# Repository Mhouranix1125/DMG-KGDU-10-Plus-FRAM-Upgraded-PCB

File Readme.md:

### Welcome! PLEASE READ EVERYTHING!

First: Shoutout to HDR. His work was extremely vital in completing this project. Take a look at his github and check out some of the cool projects he has worked on!

[HDR's Github](https://github.com/HDR)

Second: You do this entire transfer at your own risk. I am not responsible for anything that happens to your game as a result of taking on this project. This is not a beginner task, and should definitely not be taken on as a first-time solder project.  I am not affiliated with any of the companies mentioned here. I do not do this for profit. This is just a neat little thing I decided to work on. 

This project is open source. Users may use this work to iterate, or improve upon it. In doing so, please make sure you follow the Creative Common License linked below. Out of respect for HDR. Do not be a bad actor. your compliance is expected, and appreciated. DMG-KGDU-10 is an original Nintendo PCB design. I take no credit for that. 

[Creative Commons License](https://creativecommons.org/licenses/by-nc-sa/4.0/)

### What is this project about?

In simple terms - This project is an upgraded replacement circuit board for games like Pokémon Gold, Silver, and Crystal. This board utilizes FRAM instead of SRAM so you can save your games without the need for a battery. The battery is still required for the real time clock (RTC) to function. But the good news is you will not lose any save data when the battery does die. This also features a battery retainer, so you can place a CR2025 into the slot without the need for solder tabs. This also enables you to use BRAND NAME batteries. The batteries most users buy for their games have those yellow rings around them and are absolutely terrible and volatile. Brand Name batteries are a more reliable choice and will last MUCH longer. This board was designed with the United States version of the games in mind. I created this board for a few reasons. 

1. SRAM is annoying and I hate that my save data was at the mercy of a simple coin cell battery. This fixes that and allows for a very clean and professional looking mod without wires running all over the place.

2. I see tons of reddit posts of people posting their Pokemon Gold, Silver, or Crystal games in less than stellar condition. Sure, you can use jumper wires, and if you like that, it's all you. Some are beyond repair due to corrosion, broken traces, or just problems that aren't solvable. If the ROM IC, and MBC3 mapper are in good shape. This board will definitely save your game. Your games are not broken if your circuit board is in bad shape!

3. To learn.

### How can I get my hands on these boards?

In order to get your hands on these boards, you will need to download this project zip, or clone it using GIT. One of the files labeled DMG-KGDU-10+_Gerber.zip Is the completed output of the circuit board. There are a few websites you can upload this to in order to get these boards made. they are not that expensive. These are the ones I use often. But feel free to use another if you’re comfortable with them. 

Note: PLEASE ORDER THESE BOARDS WITH THE FOLLOWING SPECIFICATIONS. IF YOU DO NOT ORDER THEM CORRECTLY, THEY WILL NOT WORK, OR WILL NOT FIT!

* Thickness: 0.8mm
* Color: Your choice! Have fun!
* Surface Finish: (ENIG or Immersion Gold. They’re the same thing) , or Hard Gold (expensive). DO NOT USE ANY OTHER OPTION. 
* Castellated Holes: No
* Copper Weight: 1oz is fine. 2oz is nice but not needed.
* Golden Fingers: Yes 
* 45° finger chamfered

1. [JLCPCB:](https://jlcpcb.com/)

o This company is based in China, and has very good pricing on boards so long as you choose either green or purple. I find the best bang for your buck to be 10 boards as it's not that much more expensive than 5.

2. [Elecrow:](https://www.elecrow.com/)

o This company is based in China, the pricing is great, and pricing is similar to JLCPCB and seems consistent across all colors. So I love these guys quite a bit. 

o Note: If using Elecrow, you will need to send them an email to specify that you want Golden Fingers, and beveled 45° finger chamfered. Just give them your order number after you place it. 

3. [Osh Park:](https://oshpark.com/shared_projects/EM2j1Td4)

o Osh Park is a USA based company. Their online gerber viewer and order process is very easy. But your options are very limited. You can only get your boards in their signature deep purple color, which are quite nice. They’re also the most expensive. Their quality is good. You get less PCB’s for your money, and I noticed that it could still take a while for them to come in.

o When you order, choose the option that says: 2 oz copper, 0.8mm thickness and you should be all set. Their ordering process is more streamlined. 

### Materials

You will need the following materials to complete this build. Feel free to source these from wherever you’d like. I recommend [Digikey](https://digikey.com), or [Mouser](https://mouser.com) for most parts. just make sure the sizes for the capacitors and resistors are correct. Double check everything. 

**Bill Of Materials:**

| Reference | Part | Description | Type |
|-|-|-|-|
| U1 | Original ROM | The lower Right chip. This is the chip that holds your game and is needed from the original board. | 44 Pins |
| U2 | MBC3 | Memory Bank Controller. You can only get this from an original Cartridge | LQFP-32 |
| U3 | FM18W08 | 256kbit FRAM | SOIC-28 |
| U4 | BA6129AF | Battery Reset IC. | Get From Original Cartridge or AliExpress | SOIC-8 |
| U5 | 74LVC1G32GV,125 | 2-input OR Gate | TSOP-5 |
| C1, C2, C3, C6, C7 | CL10B104KO8NNNC | 0.1uF Capacitor | 0603 |
| C4, C5 | CL10C150JB8NNNC | 15pF Capacitor | 0603 |
| R1 | RC0603FR-07330KL | 330K Ω Resistor | 0603 |
| R2 | RC0603FR-0710KL | 10K Ω Resistor | 0603 |
| R3 | RC0603FR-071KL | 1K Ω Resistor | 0603 |
| X1 | R26-32.768-12.5-10PPM 20PPM seems to work fine as well. | 32.768 kHz Crystal. | Buy or get from original Cartridge |
| RTC Crystal | Batt 2025 | BK-6219-TR | CR2025 Battery Retainer | Battery Retainer |

Some Tips

1). This should not be your first major solder project. Do not attempt to do this without any practice, or you risk ruining your game. 

2). Everything is pretty straight forward. Make sure you’re good with working on small components. Capacitors and resistors are not easy to solder if you’re new to this. Solder paste and hot air can help you out a lot with that process. 

3). The CR2025 battery may sometimes may not make amazing contact with the large circle pad. This is because it is ever so slightly recessed into the board. This can be fixed in a variety of ways. Super easy, and is pretty much a non issue if you just follow one of the following two ways.

My way of solving this issue is cutting out a thin piece of nickel strip (I try to make it circular in shape, and a bit smaller than the edges of the circle pad. And I lay it down flat and solder it in place before installing the BK-6219-TR retainer. Make sure you solder in the retainer so you can place the battery in from the top side of the board. If you do it upside down, getting the battery in will be annoying because the ROM IC gets in the way. 

Another way, if you don’t want to cover the pad with solder is Makhos way. Makho uses a piece of copper tape on the circle pad, rather than soldering in the nickel strip that I use. It’s nice if you don’t want to get solder on the circle pad. I personally don’t mind but the choice is yours. 

Good luck! Be sure to post your successes, and feel free to ask me any questions!

### Images

# Front

# Back

### Changes

Rev 1.1 
- Removed R1 Jumper Resistor. It was not needed.
- Added Text for some parts to help with clarity. The BOM should still be the ultimate source for info. 
- Moved a few capacitors around so they're easier to manage.
- Moved R3 so it would be easier to manage once the battery retainer is soldered in if need be.
- General cleanup.

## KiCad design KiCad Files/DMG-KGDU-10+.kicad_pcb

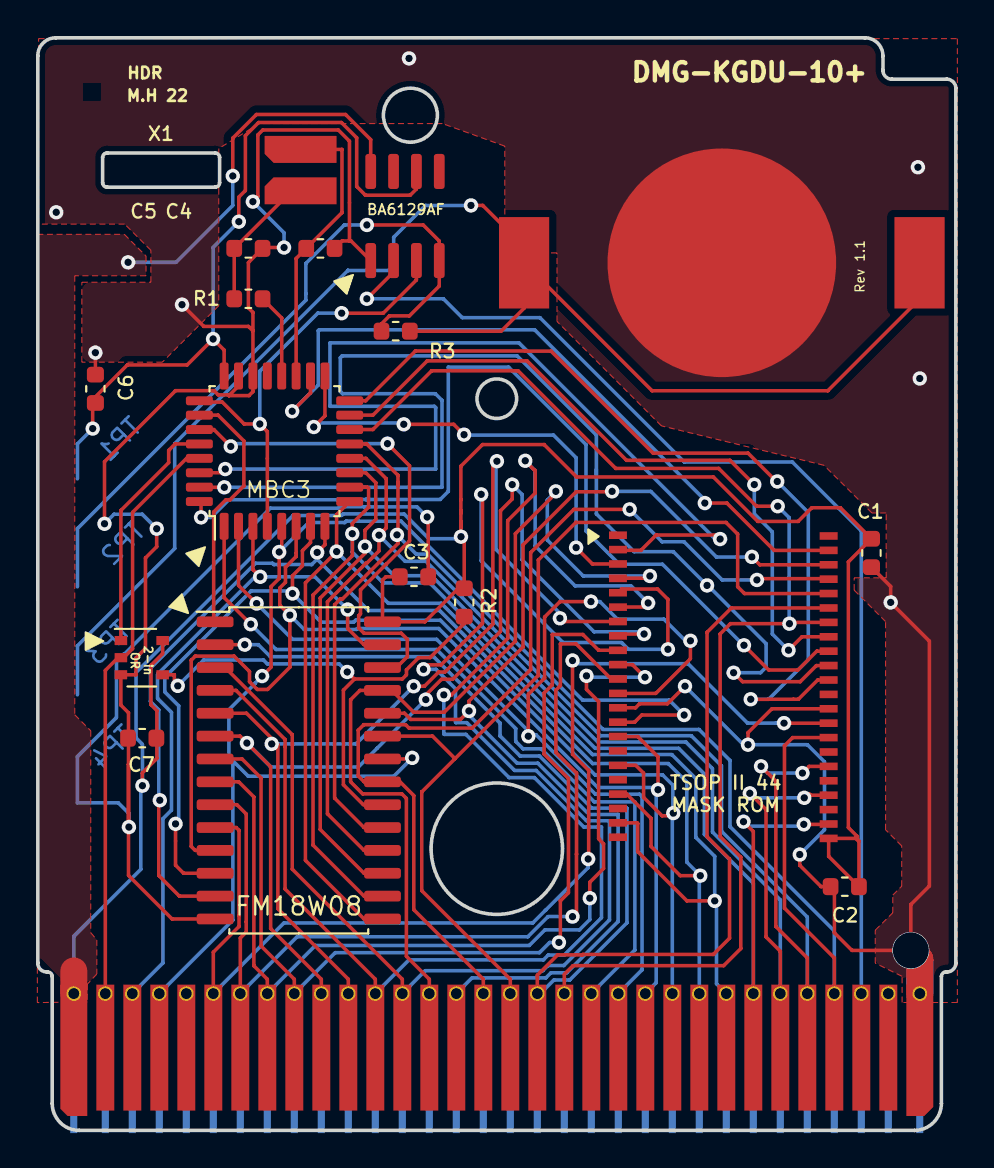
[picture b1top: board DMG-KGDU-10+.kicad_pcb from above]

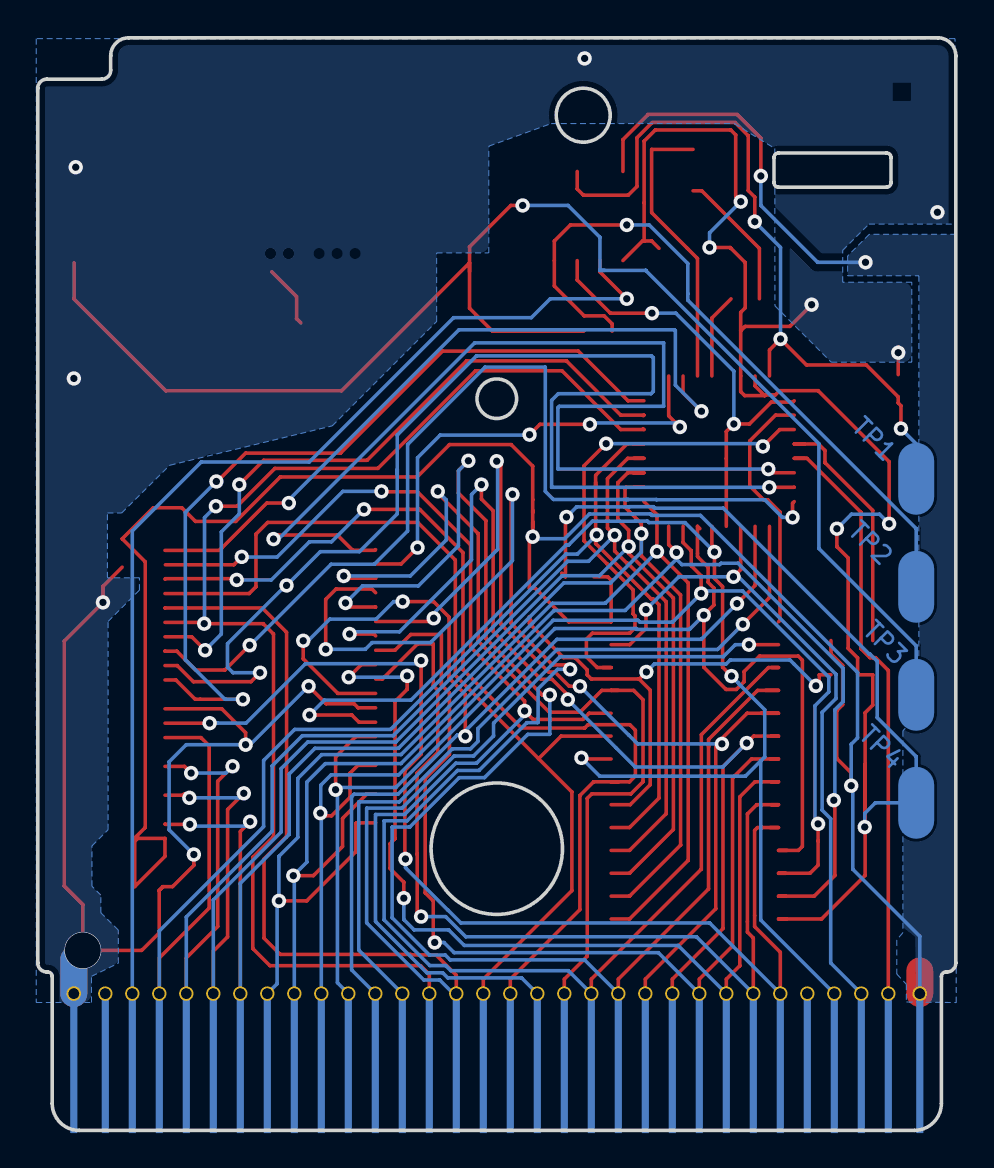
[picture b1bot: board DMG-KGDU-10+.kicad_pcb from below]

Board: 2 copper layers, 51.0 x 60.7 mm, 25 parts (5 on the bottom side), 48 nets.

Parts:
B1: Battery_Cell; BK-6219-TR
C1, C2, C3, C6, C7: 0.1 uF; C_0603_1608Metric
C4, C5: 15 pF; C_0603_1608Metric
GNDPAD1: Nintendo_3x3_GNDPad
L0: CASTELLATIONS TSOP-II 22P; 22_SMD_PADs
PAD*: GBA-ProductionIndicator
R0: CASTELLATIONS TSOP-II 22P; 22_SMD_PADs
R1: 330Kohm; R_0603_1608Metric
R2: 10 Kohm; R_0603_1608Metric
R3: 1 Kohm; R_0603_1608Metric
TP1: RTC_VOUT; GameBoy_Testpoint
TP2: Battery_Positive_After_Resistor; GameBoy_Testpoint
TP3: Battery_Positive; GameBoy_Testpoint
TP4: Ground; GameBoy_Testpoint
U0: CartBus; GameBoy_GamePak_CGB-002_P1.50mm_Edge
U2: MBC3
U3: FM18W08; SOIC-28W_7.5x17.9mm_P1.27mm
U4: BA6129AF; SOIC-8_3.9x4.9mm_P1.27mm
U5: 74LVC1G32; TSOP-6_1.65x3.05mm_P0.95mm
Y1: Crystal; Resonator_SMD_muRata_CDSCB-2pin_4.5x2.0mm_HandSoldering

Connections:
#CE: R2.1, U3.20, U5.4
A0: R0.14, U0.6, U3.10
A1: L0.12, U0.7, U3.9
A2: L0.13, U0.8, U3.8
A3: L0.14, U0.9, U3.7
A4: L0.15, U0.10, U3.6
A5: L0.16, U0.11, U3.5
A6: L0.17, U0.12, U3.4
A7: L0.18, U0.13, U3.3
A8: L0.19, U0.14, U3.25
A9: R0.3, U0.15, U3.24
A10: R0.4, U0.16, U3.21
A11: R0.5, U0.17, U3.23
A12: R0.6, U0.18, U3.2
A13: R0.7, U0.19, U2.14
A14: U0.20, U2.1
A15: L0.11, U0.21, U2.2
AA13: U2.27, U3.26
AA14: U2.26, U3.1
BT+: B1.1, R3.1, TP3.1
CLK: U0.2, U2.29, U5.2
D0: L0.8, U0.22, U2.6, U3.11
D1: L0.6, U0.23, U2.7, U3.12
D2: L0.4, U0.24, U2.8, U3.13
D3: L0.2, U0.25, U2.9, U3.15
D4: R0.21, U0.26, U2.10, U3.16
D5: R0.19, U0.27, U2.11, U3.17
D6: R0.17, U0.28, U2.12, U3.18
D7: R0.15, U0.29, U2.13, U3.19
GND: B1.2, C1.1, C2.2, C3.1, C4.2, C5.1, C6.2, C7.1, L0.10, R0.13, TP4.1, U0.32, U2.22, U2.23, U3.14, U4.1, U5.3
unnamed: C5.2, R1.2, Y1.1
PWR: C6.1, TP1.1, U2.24, U4.6
RA14: R0.8, U2.15
RA15: R0.9, U2.32
RA16: R0.10, U2.31
RA17: R0.11, U2.16
RA18: L0.20, U2.17
RA19: L0.21, U2.30
RA20: R0.2, U2.18
RESET: U0.30, U4.2
VCC: C1.2, C2.1, C3.2, C7.2, R0.22, R2.2, U0.1, U3.28, U4.8, U5.6
Vbatt: R3.2, TP2.1, U4.4
XIN: C4.1, U2.19, Y1.2
XOUT: R1.1, U2.20
\RAMCS: U2.28, U5.1
\RD: L0.9, U0.4, U2.5, U3.22
\RST: U2.4, U2.25, U4.3
\WR: U0.3, U2.3, U3.27

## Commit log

2022-10-20 Rerouted tracks to work with an original Mask Rom
2022-11-11 Replaced 3 input or-gate with a 2-input one.
2022-11-22 Credit to HDR & License
2022-11-30 Added stuff for public use.
2022-11-30 Added licenses
2023-01-17 Rev 1.1 update
